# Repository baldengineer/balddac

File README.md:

# Bald DAC Wing

Open hardware KiCad project for a two-channel, high-speed digital-to-analog converter (DAC) board.

The design is built around the Analog Devices AD5447 dual 12-bit multiplying current-output DAC and includes fast output amplification, a precision reference, digital interface logic, coaxial outputs, and test points. Revision 1 has been prepared for fabrication.

## Features

- Dual 12-bit current-output DAC channels
- AD8065 high-speed output amplifier stages
- REF3425 2.5 V voltage reference
- Parallel digital interface with registered/control logic
- Separate coaxial outputs for DAC A and DAC B
- 3.3 V digital power and dedicated analog/reference power nets
- Four-layer PCB stackup with internal copper planes
- Custom KiCad symbols for project-specific parts

## Status

Revision 1 was sent to fabrication.

## License

This project is released under the [MIT License](LICENSE).

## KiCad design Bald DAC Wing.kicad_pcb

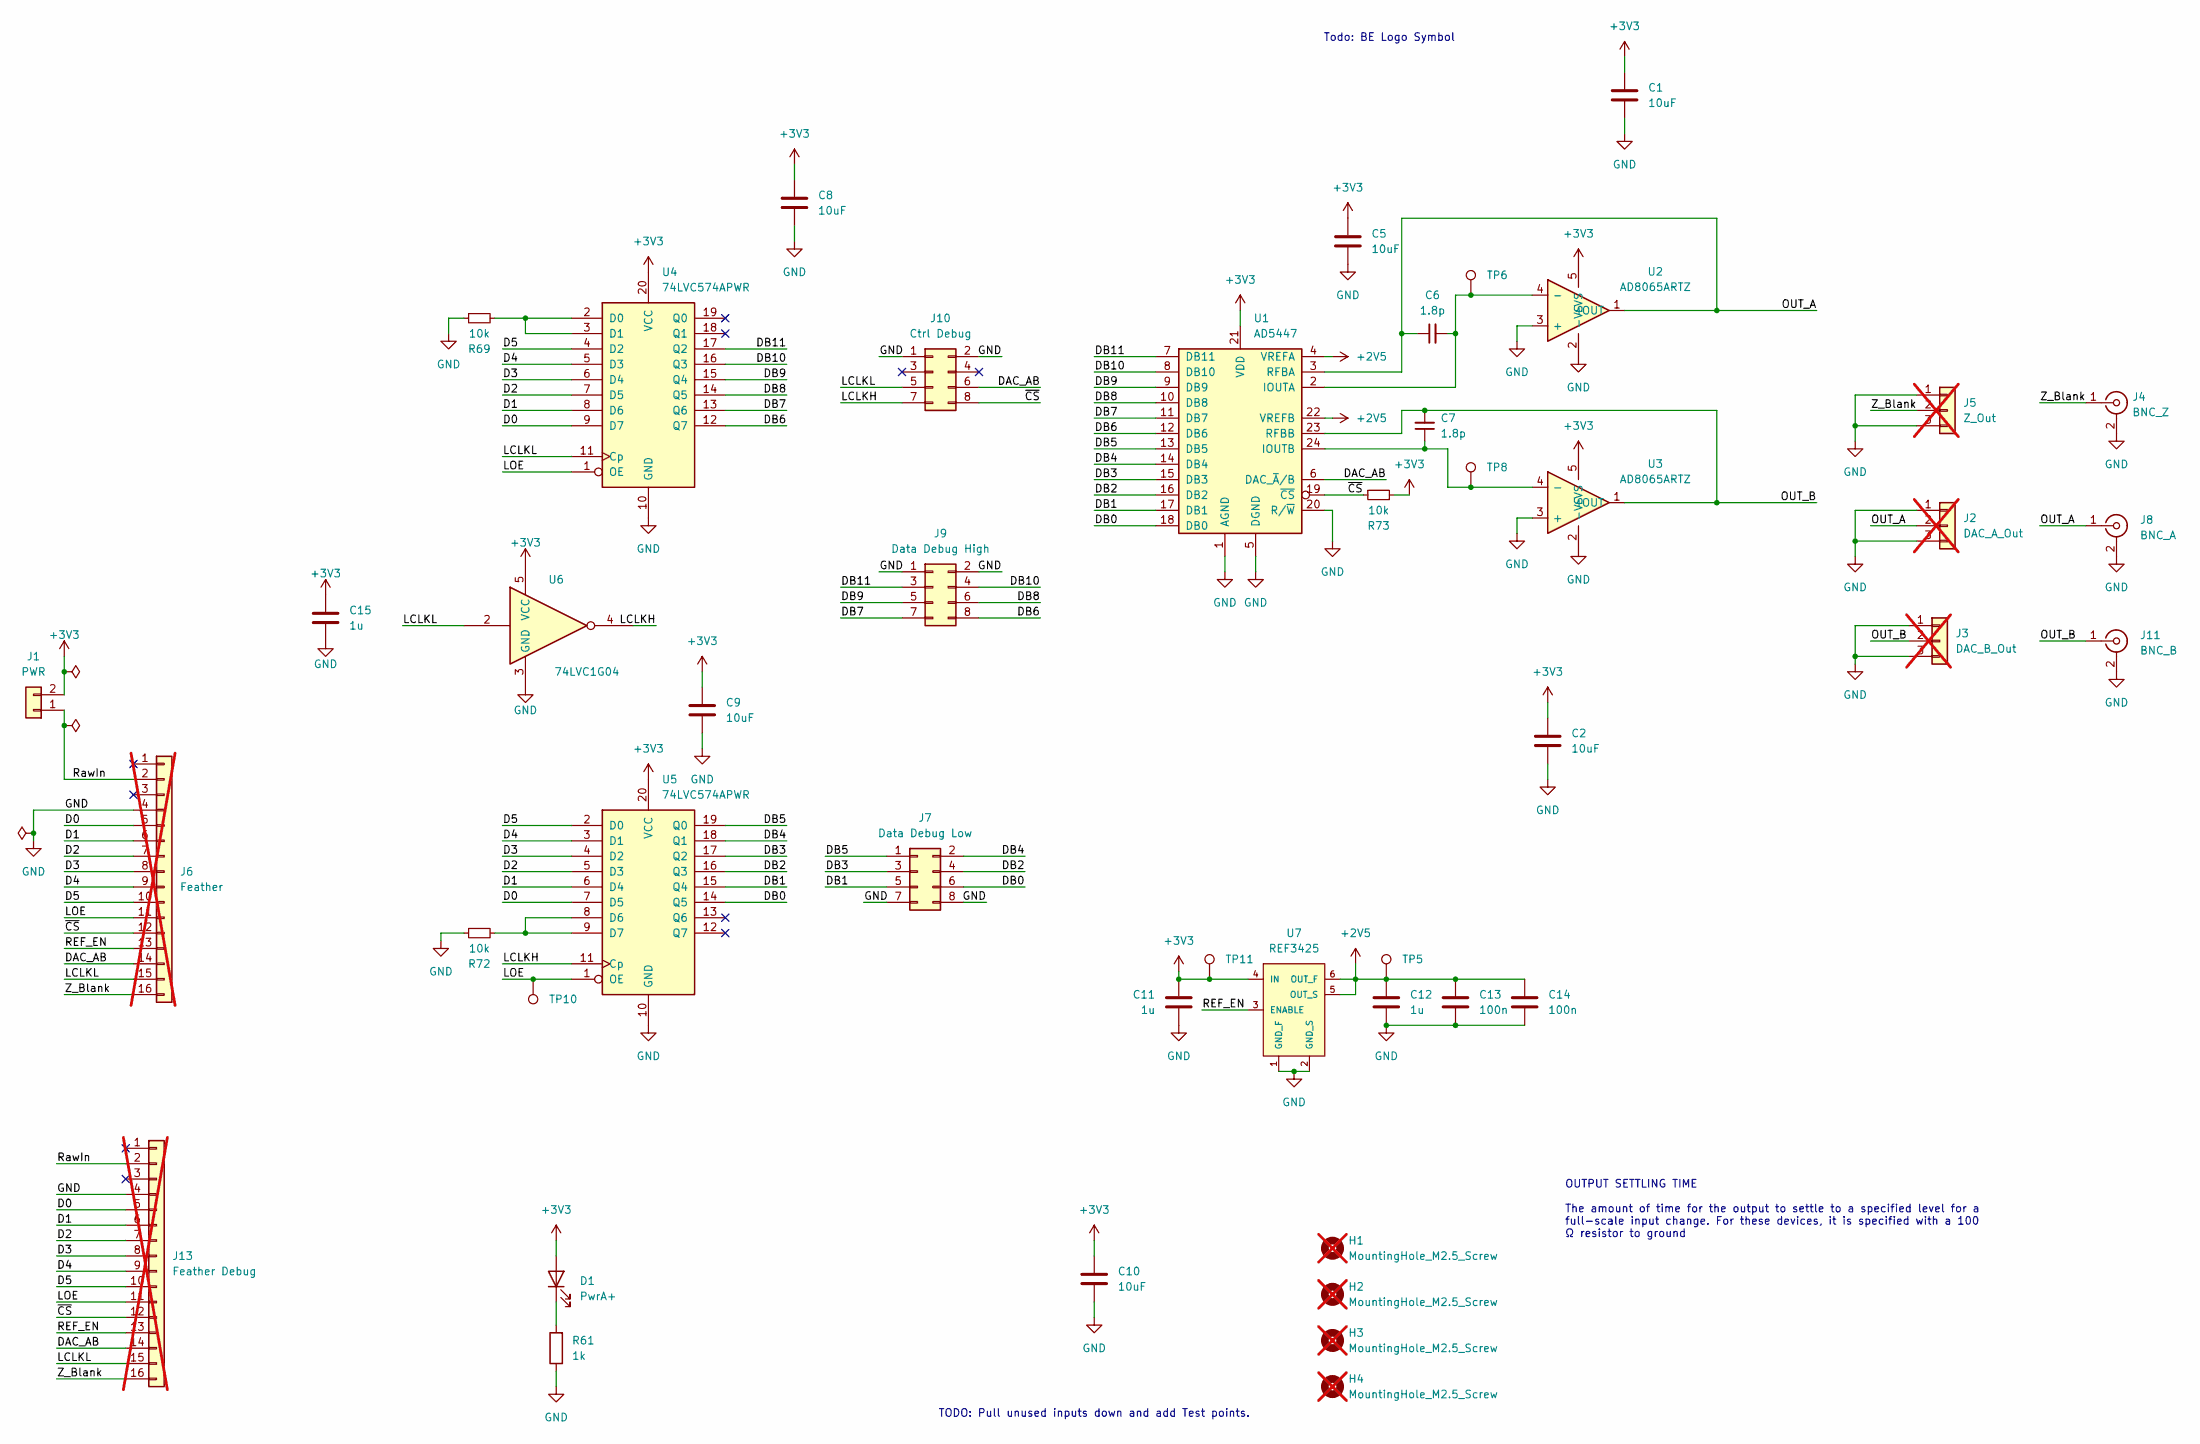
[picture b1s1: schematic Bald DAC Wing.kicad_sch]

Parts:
C1, C2, C5, C8, C9, C10: 10uF; C_0805_2012Metric_Pad1.18x1.45mm_HandSolder; LCSC C15850
C6, C7: 1.8p; C_0603_1608Metric_Pad1.08x0.95mm_HandSolder; LCSC C282244
C11, C12, C15: 1u; C_0805_2012Metric_Pad1.18x1.45mm_HandSolder; LCSC C15850
C13, C14: 100n; C_0402_1005Metric_Pad0.74x0.62mm_HandSolder; LCSC C307331
D1: PwrA+; LED_0805_2012Metric_Pad1.15x1.40mm_HandSolder; LCSC C2297
H1, H2, H3, H4: MountingHole_M2.5_Screw; MountingHole_2.7mm_M2.5; LCSC N/A; not fitted
J1: PWR; PinHeader_1x02_P2.54mm_Vertical
J2: DAC_A_Out; PinHeader_1x03_P2.54mm_Vertical; LCSC N/A; not fitted
J3: DAC_B_Out; PinHeader_1x03_P2.54mm_Vertical; LCSC N/A; not fitted
J4: BNC_Z; Molex_73100-0105_BNC_RA; Mouser 538-73100-0105
J5: Z_Out; PinHeader_1x03_P2.54mm_Vertical; LCSC N/A; not fitted
J6: Feather; PinSocket_1x16_P2.54mm_Vertical; not fitted
J7: Data Debug Low; PinHeader_2x04_P2.54mm_Vertical
J8: BNC_A; Molex_73100-0105_BNC_RA; Mouser 538-73100-0105
J9: Data Debug High; PinHeader_2x04_P2.54mm_Vertical
J10: Ctrl Debug; PinHeader_2x04_P2.54mm_Vertical
J11: BNC_B; Molex_73100-0105_BNC_RA; Mouser 538-73100-0105
J13: Feather Debug; PinSocket_1x16_P2.54mm_Vertical; not fitted
R61: 1k; R_0603_1608Metric_Pad0.98x0.95mm_HandSolder; LCSC C21190
R69, R72, R73: 10k; R_0603_1608Metric_Pad0.98x0.95mm_HandSolder; LCSC C25804
TP5, TP6, TP8, TP10, TP11: TestPoint_Harwin; Harwin-S1751-46-Test-Point; LCSC C3029083
U1: AD5447; TSSOP-24_4.4x7.8mm_P0.65mm; LCSC C514217
U2, U3: AD8065ARTZ; SOT-23-5; LCSC C9648
U4, U5: 74LVC574APWR; TSSOP-20_4.4x6.5mm_P0.65mm; LCSC C7672
U6: 74LVC1G04; SOT-23-5; LCSC C7827
U7: REF3425; SOT-23-6; LCSC C187836

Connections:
+2V5: C12.1, C13.1, C14.1, TP5.1 (1_1), U1.4 (VREFA), U1.22 (VREFB), U7.5 (OUT_S), U7.6 (OUT_F)
+3V3: C1.1, C2.1, C5.1, C8.1, C9.1, C10.1, C11.1, C15.1, D1.2 (A), J1.2, R73.2, TP11.1 (1_1), U1.21 (VDD), U2.5 (+VS), U3.5 (+VS), U4.20 (VCC), U5.20 (VCC), U6.5 (VCC), U7.4 (IN)
/D0: J6.5, J13.5, U4.9 (D7), U5.7 (D5)
/D1: J6.6, J13.6, U4.8 (D6), U5.6 (D4)
/D2: J6.7, J13.7, U4.7 (D5), U5.5 (D3)
/D3: J6.8, J13.8, U4.6 (D4), U5.4 (D2)
/D4: J6.9, J13.9, U4.5 (D3), U5.3 (D1)
/D5: J6.10, J13.10, U4.4 (D2), U5.2 (D0)
/DAC_AB: J6.14, J10.6, J13.14, U1.6 (DAC_~A/B)
/DB0: J7.6, U1.18 (DB0), U5.14 (Q5)
/DB1: J7.5, U1.17 (DB1), U5.15 (Q4)
/DB2: J7.4, U1.16 (DB2), U5.16 (Q3)
/DB3: J7.3, U1.15 (DB3), U5.17 (Q2)
/DB4: J7.2, U1.14 (DB4), U5.18 (Q1)
/DB5: J7.1, U1.13 (DB5), U5.19 (Q0)
/DB6: J9.8, U1.12 (DB6), U4.12 (Q7)
/DB7: J9.7, U1.11 (DB7), U4.13 (Q6)
/DB8: J9.6, U1.10 (DB8), U4.14 (Q5)
/DB9: J9.5, U1.9 (DB9), U4.15 (Q4)
/DB10: J9.4, U1.8 (DB10), U4.16 (Q3)
/DB11: J9.3, U1.7 (DB11), U4.17 (Q2)
/LCLKH: J10.7, U5.11 (Cp), U6.4
/LCLKL: J6.15, J10.5, J13.15, U4.11 (Cp), U6.2
/LOE: J6.11, J13.11, TP10.1 (1_1), U4.1 (OE), U5.1 (OE)
/OUT_A: C6.1, J2.2, J8.1 (In), U1.3 (RFBA), U2.1 (OUT)
/OUT_B: C7.2, J3.2, J11.1 (In), U1.23 (RFBB), U3.1 (OUT)
/REF_EN: J6.13, J13.13, U7.3 (ENABLE)
/RawIn: J1.1, J6.2, J13.2
/Z_Blank: J4.1 (In), J5.2, J6.16, J13.16
/~CS: J6.12, J10.8, J13.12, R73.1, U1.19 (~CS)
GND: C1.2, C2.2, C5.2, C8.2, C9.2, C10.2, C11.2, C12.2, C13.2, C14.2, C15.2, J2.1, J2.3, J3.1, J3.3, J4.2 (Ext), J5.1, J5.3, J6.4, J7.7, J7.8, J8.2 (Ext), J9.1, J9.2, J10.1, J10.2, J11.2 (Ext), J13.4, R61.1, R69.1, R72.1, U1.1 (AGND), U1.5 (DGND), U1.20 (R/~W), U2.2 (-VS), U2.3 (+), U3.2 (-VS), U3.3 (+), U4.10 (GND), U5.10 (GND), U6.3 (GND), U7.1 (GND_F), U7.2 (GND_S)
unnamed: D1.1 (K), R61.2
unnamed: C6.2, TP6.1 (1_1), U1.2 (IOUTA), U2.4 (-)
unnamed: C7.1, TP8.1 (1_1), U1.24 (IOUTB), U3.4 (-)
unnamed: R69.2, U4.2 (D0), U4.3 (D1)
unnamed: R72.2, U5.8 (D6), U5.9 (D7)

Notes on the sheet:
OUTPUT SETTLING TIME The amount of time for the output to settle to a specified level for a full-scale input change. For these devices, it is specified with a 100 Ω resistor to ground
Todo: BE Logo Symbol
TODO: Pull unused inputs down and add Test points.

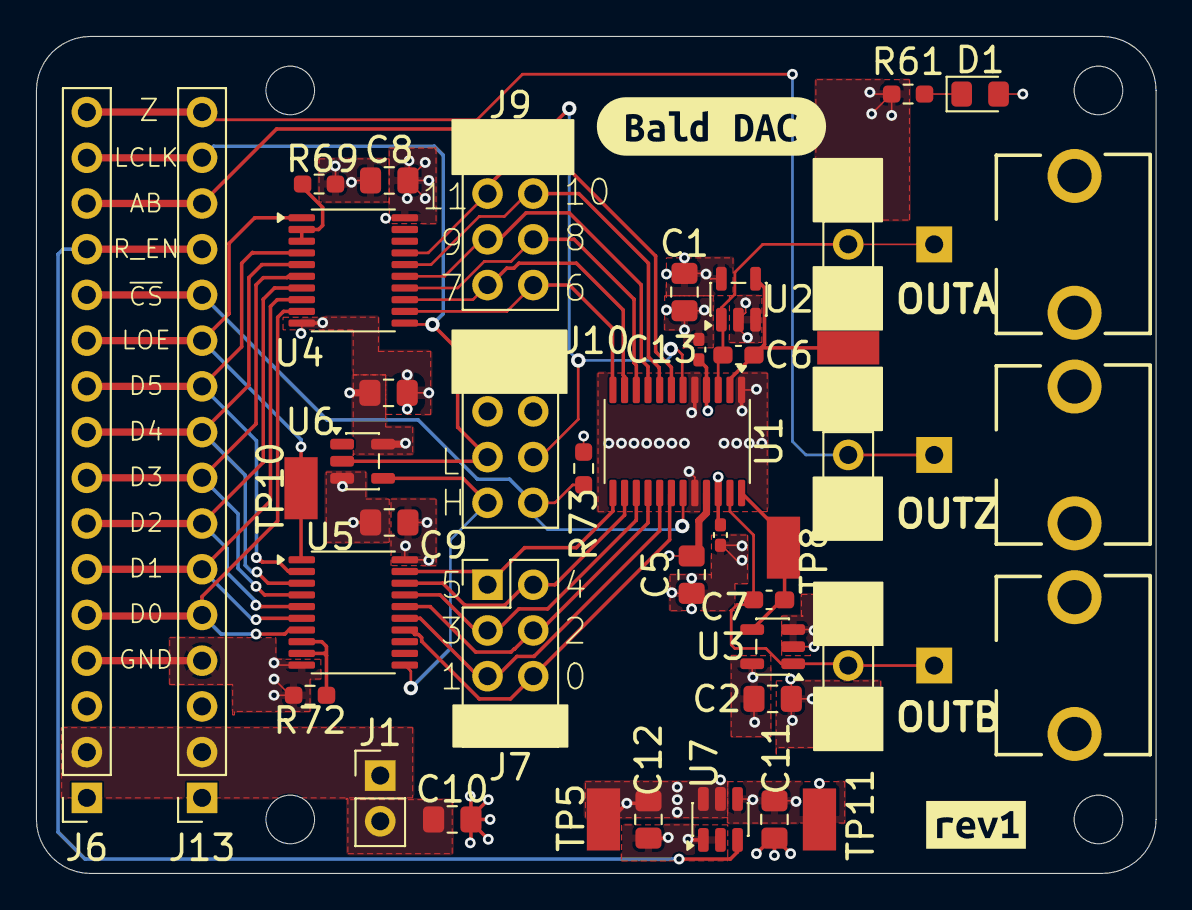
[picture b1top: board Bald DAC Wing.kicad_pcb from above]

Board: 4 copper layers, 62.2 x 46.5 mm, 48 parts (0 on the bottom side), 36 nets.

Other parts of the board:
kibuzzard-6AB056B3: G***; kibuzzard-6AB056B3
kibuzzard-6AB05686: G***; kibuzzard-6AB05686
